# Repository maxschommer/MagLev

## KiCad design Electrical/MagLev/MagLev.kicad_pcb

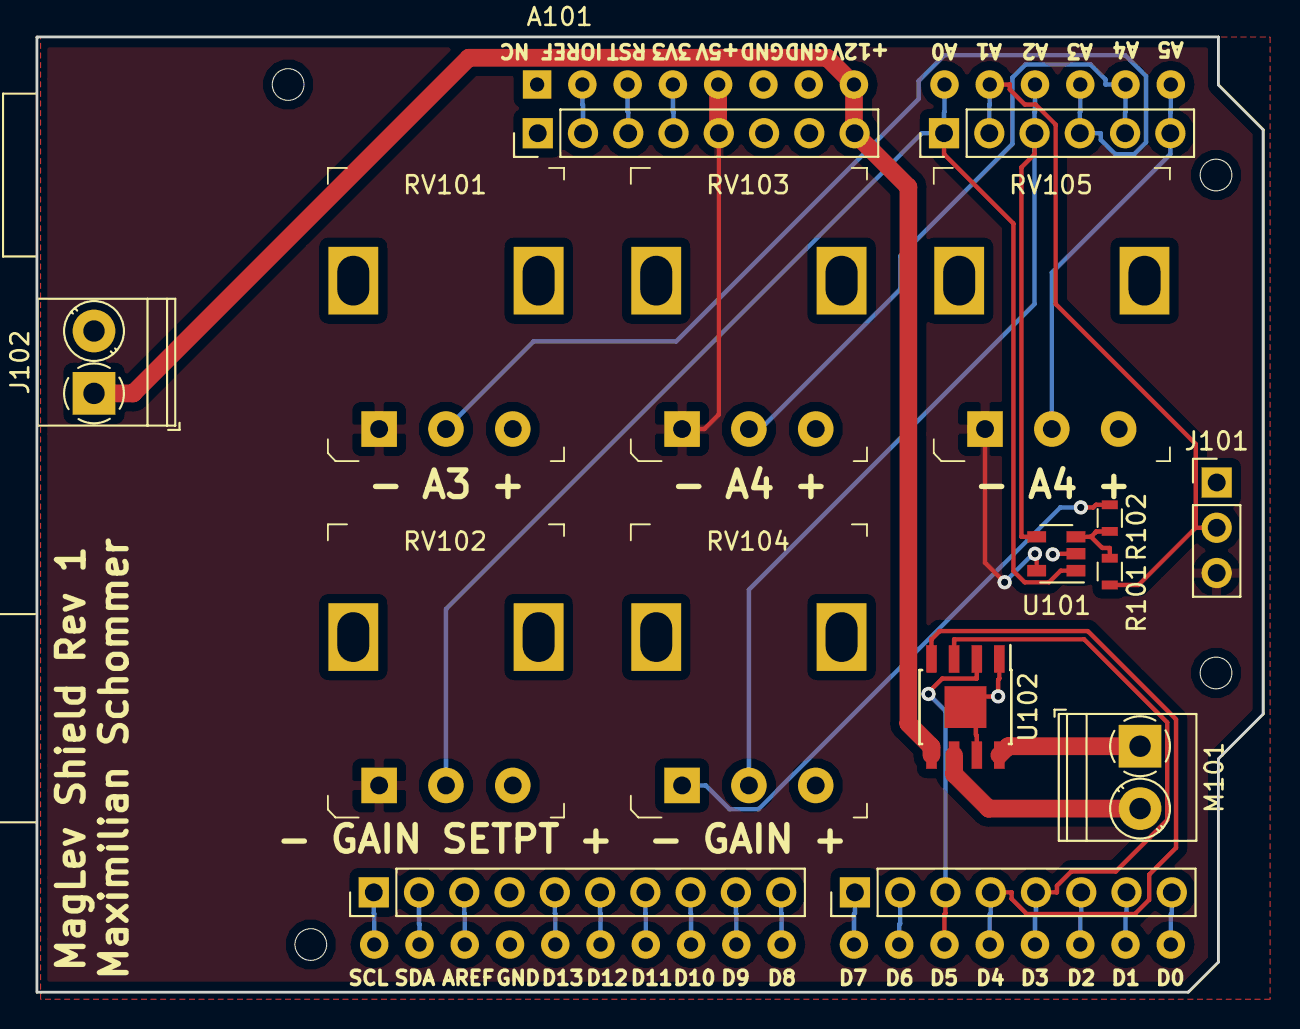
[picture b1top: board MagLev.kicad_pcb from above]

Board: 2 copper layers, 68.8 x 53.6 mm, 17 parts (0 on the bottom side), 33 nets.

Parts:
A101: Arduino_UNO_R3; Arduino_UNO_R3_WithMountingHoles
J101: Conn_01x03; Pin_Header_Straight_1x03_Pitch2.54mm
J102: Screw_Terminal_01x02; TerminalBlock_Phoenix_PT-1,5-2-3.5-H_1x02_P3.50mm_Horizontal
J103: Conn_01x10_Male; Pin_Header_Straight_1x10_Pitch2.54mm
J104, J105: Conn_01x08_Male; Pin_Header_Straight_1x08_Pitch2.54mm
J106: Conn_01x06_Male; Pin_Header_Straight_1x06_Pitch2.54mm
M101: Motor_DC; TerminalBlock_Phoenix_PT-1,5-2-3.5-H_1x02_P3.50mm_Horizontal
R101, R102: 1k; R_0603
RV101, RV102, RV103, RV104, RV105: 10k; Potentiometer_P120PK-Y25BR10K
U101: LMV321; SOT-23-5
U102: DRV8872DDAR; SOIC-8-1EP_3.9x4.9mm_Pitch1.27mm

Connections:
+5V: A101.5, J101.3, J105.5, RV101.1, RV102.1, RV103.1, RV105.1, U101.5
+12V: A101.8, J102.1, J105.8, U102.5
/A0: A101.9, J106.1, RV102.2, U101.1
/A1: A101.10, J101.2, J106.2, R101.2
/A2: A101.11, J106.3, RV104.2, U101.4
/IN1: A101.18, J104.5, U102.3
/IN2: A101.20, J104.3, U102.2
/POT_1: A101.12, J106.4, RV101.2
/POT_2: A101.13, J106.5, RV103.2
/POT_3: A101.14, J106.6, RV105.2
/P_2: A101.2, J105.2
/P_3: A101.3, J105.3
/P_4: A101.4, J105.4
/P_15: A101.15, J104.8
/P_16: A101.16, J104.7
/P_17: A101.17, J104.6
/P_19: A101.19, J104.4, U102.4
/P_21: A101.21, J104.2
/P_22: A101.22, J104.1
/P_23: A101.23, J103.10
/P_24: A101.24, J103.9
/P_25: A101.25, J103.8
/P_26: A101.26, J103.7
/P_27: A101.27, J103.6
/P_28: A101.28, J103.5
/P_30: A101.30, J103.3
/P_31: A101.31, J103.2
/P_32: A101.32, J103.1
GND: A101.6, A101.7, A101.29, J101.1, J102.2, J103.4, J105.6, J105.7, RV101.3, RV102.3, RV103.3, RV105.3, U101.2, U102.1, U102.7, U102.9
unnamed: M101.1, U102.8
unnamed: M101.2, U102.6
unnamed: R101.1, R102.2, U101.3
unnamed: R102.1, RV104.1

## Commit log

2019-02-03 Almost stable levitation
2019-03-23 Tuned removeElectromagnetEffect using derivitive
2019-03-23 Working!
2019-04-18 Made Rev1
